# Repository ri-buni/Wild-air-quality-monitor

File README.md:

# Wild-air-quality-monitor
An air quality monitor I've decided to make because of how bad the air in my city can be sometimes.
It has sht41, sgp40, scd41, PMS5003 as sensors for temperature, humidity, VOC CO2 and PM, 2"42 display and esp32 devkitc

# CAD
Made in Fusion360.

# PCB
Made in KiCad.

Schematic:

PCB:

# Firmware was made by Claude Code

Display looks like this:

# BOM

| Item | Description | Qty | Unit Price | Line Total | Source |
|---|---|---|---|---|---|
| PCB | Custom 2-layer PCB | 1 | $12.00 | $12.00 | [JLCPCB](https://jlcpcb.com/) |
| ESP32-S3 DevKitC | MCU dev board | 1 | $5.00 | $5.00 | [AliExpress](https://aliexpress.ru/item/1005007820190456.html?sku_id=12000058365460928) |
| 2.42" OLED | 128x64 SSD1309, I2C/SPI | 1 | $12.00 | $12.00 | [AliExpress](https://aliexpress.ru/item/4000002579405.html?sku_id=12000037978104081) |
| SGP40 | VOC gas sensor module | 1 | $5.00 | $5.00 | [AliExpress](https://aliexpress.ru/item/1005008380047927.html?sku_id=12000056592935021) |
| SCD41 | CO2 + temp/humidity sensor | 1 | $14.00 | $14.00 | [AliExpress](https://aliexpress.ru/item/1005010621571588.html?sku_id=12000053002326414) |
| SHT41 | Temp/humidity sensor | 1 | $1.50 | $1.50 | [AliExpress](https://aliexpress.ru/item/1005008842184215.html?sku_id=12000057743184144) |
| Li-ion battery | 500mAh 3.7V (502535) | 1 | $5.10 | $5.10 | [AliExpress](https://aliexpress.ru/item/1005006462526013.html?sku_id=12000037283411655) |
| TP4056 | Li-ion charger module | 1 | $0.50 | $0.50 | [AliExpress](https://aliexpress.ru/item/32453058256.html?sku_id=12000052763412620) |
| PMS5003 | Laser PM2.5 sensor | 1 | $13.20 | $13.20 | [AliExpress](https://aliexpress.ru/item/32772775425.html?sku_id=12000027208101193) |
| **GRAND TOTAL** |  |  |  | **$68.30** |  |

# Details:

I've used this tutorial as a reference: https://howtomechatronics.com/projects/diy-air-quality-monitor-pm2-5-co2-voc-ozone-temp-hum-arduino-meter/

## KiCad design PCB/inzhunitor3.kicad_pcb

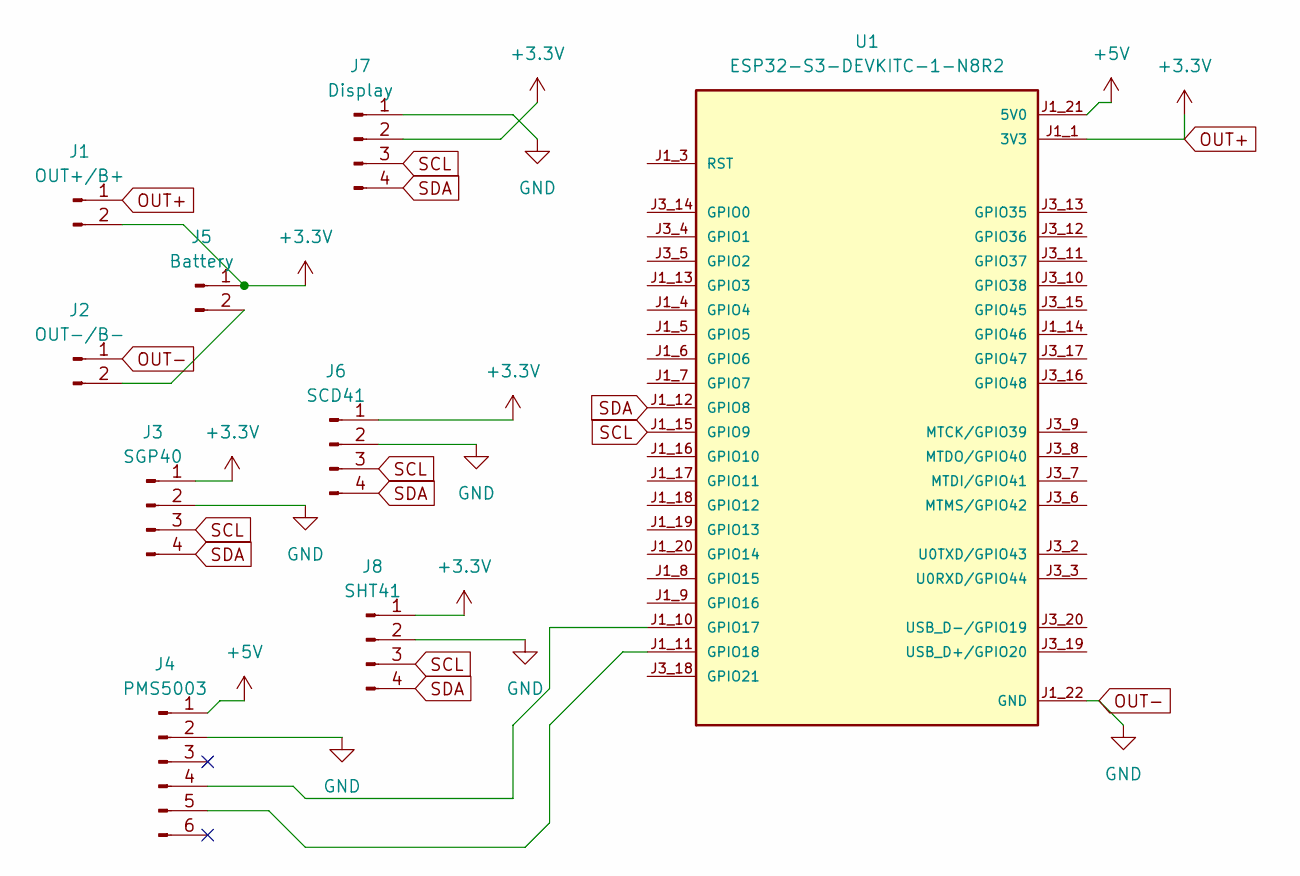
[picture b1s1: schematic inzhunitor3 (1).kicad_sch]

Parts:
J1: OUT+/B+; PinHeader_1x02_P2.54mm_Vertical
J2: OUT-/B-; PinHeader_1x02_P2.54mm_Vertical
J3: SGP40; PinHeader_1x04_P2.54mm_Vertical
J4: PMS5003; PinHeader_1x06_P2.54mm_Vertical
J5: Battery; PinHeader_1x02_P2.54mm_Vertical
J6: SCD41; PinHeader_1x04_P2.54mm_Vertical
J7: Display; PinHeader_1x04_P2.54mm_Vertical
J8: SHT41; PinHeader_1x04_P2.54mm_Vertical
U1: ESP32-S3-DEVKITC-1-N8R2; XCVR_ESP32-S3-DEVKITC-1-N8R2; PARTREV V1

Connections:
+5V: J4.1, U1.J1_21 (5V0)
unnamed: J2.2, J5.2
unnamed: J4.4, U1.J1_10 (GPIO17)
unnamed: J4.5, U1.J1_11 (GPIO18)
OUT+: J1.1, J1.2, J3.1, J5.1, J6.1, J7.2, J8.1, U1.J1_1 (3V3), U1.J1_2 (3V3)
OUT-: J2.1, J3.2, J4.2, J6.2, J7.1, J8.2, U1.J1_22 (GND), U1.J3_1 (GND), U1.J3_21 (GND), U1.J3_22 (GND)
SCL: J3.3, J6.3, J7.3, J8.3, U1.J1_15 (GPIO9)
SDA: J3.4, J6.4, J7.4, J8.4, U1.J1_12 (GPIO8)

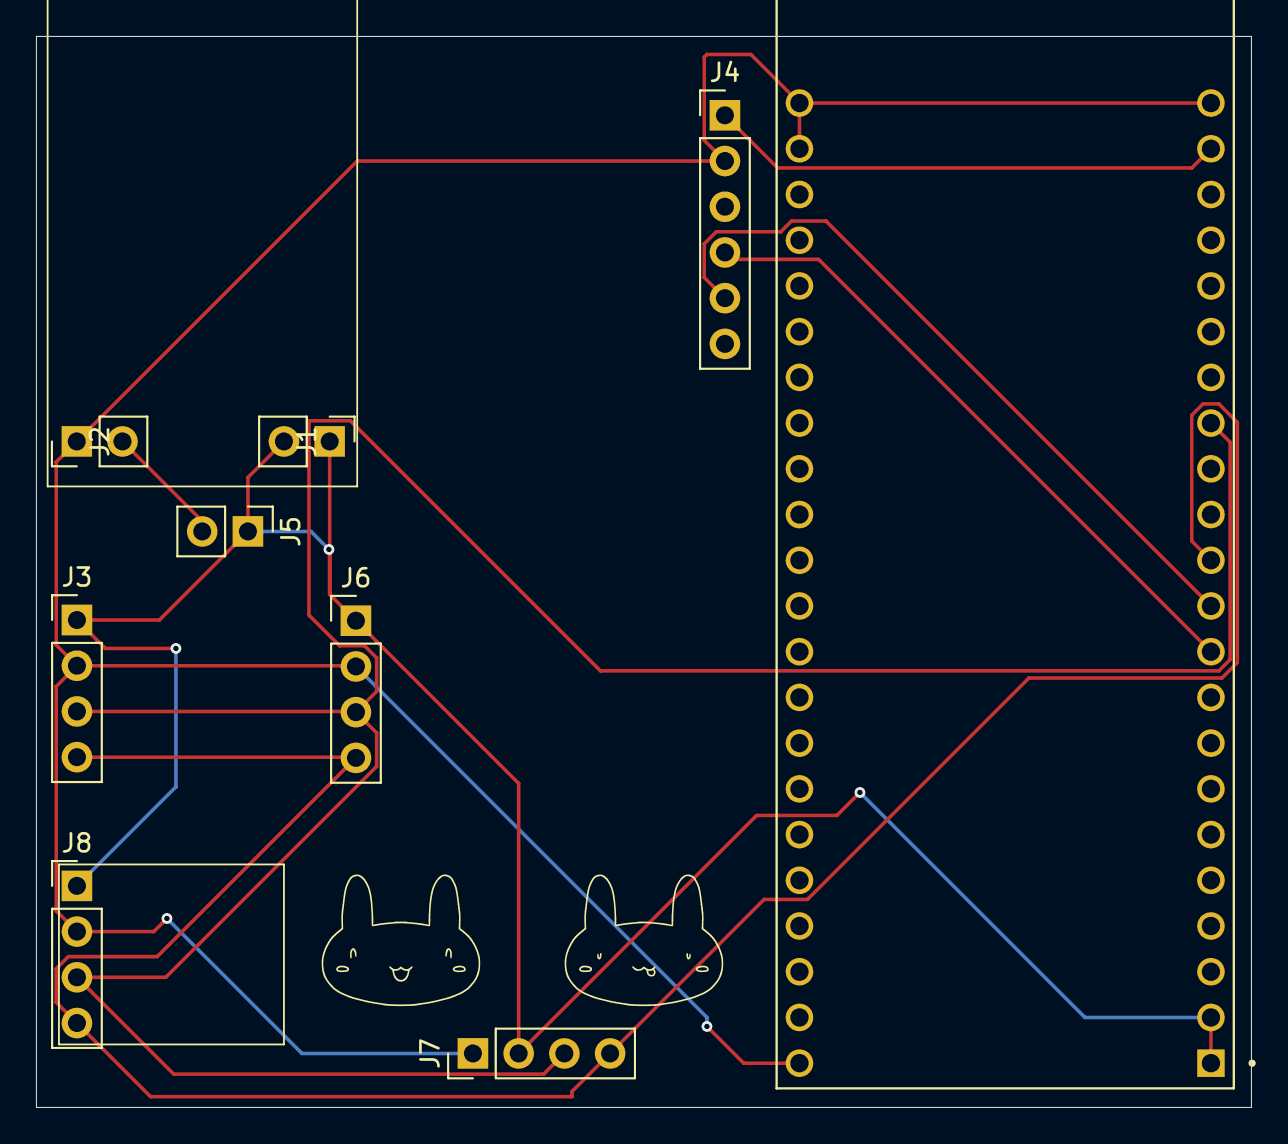
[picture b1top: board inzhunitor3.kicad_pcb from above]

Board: 2 copper layers, 67.5 x 59.5 mm, 9 parts (0 on the bottom side), 8 nets.

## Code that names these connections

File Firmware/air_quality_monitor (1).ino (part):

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 *   - U8g2
 *
 * Wiring (I2C): SCD41 / SHT41 / SGP40 / OLED share one bus.
 *   SDA = GPIO8, SCL = GPIO9 (ESP32-S3 DevKitC defaults)
 *   Addresses: SCD41 0x62 | SHT41 0x44 | SGP40 0x59 | OLED 0x3C
 *
 * Wiring (PMS5003 UART, 5V VCC, 3.3V logic - safe for ESP32-S3 RX):
 *   PMS5003 TX (pin 5) -> ESP32 GPIO17 (PMS_RX)
 *   PMS5003 RX (pin 4) -> ESP32 GPIO18 (PMS_TX, optional - for sleep/wake cmds)
 *   PMS5003 VCC -> 5V    GND -> GND
 *   SET / RESET left floating (internal pull-ups keep the sensor running)
 */
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
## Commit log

2026-06-07 Create a
2026-06-07 Create sAsad
2026-06-07 Create ss
2026-06-17 Create s
